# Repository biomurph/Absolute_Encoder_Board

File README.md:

#DEVELOPMENT BRANCH

# Absolute Encoder Board
Welcome to the Open-Source Absolute Encoder Board Repository. Here you will find hardware designs and files that support the Absolute Encoder. The [GrayCode Arduino Library](https://github.com/biomurph/GrayCode) is available for installation via the Arduino IDE, just do a search for GrayCode in the Libraries Manager 

## What is it?
Encoders come in different types. Most people are familiar with [quadrature encoders](https://en.wikipedia.org/wiki/Incremental_encoder#Quadrature_outputs), which use two pins that change state sequentially in different order depending on the direction of rotation. One of the limitations of quadrature is that a microcontroller needs to be paying attention (usually with pin-change interrupts) in order to keep track of each step and count accordingly CW or CCW steps. In certain applications, the need for interrupts and constant attention to the encoder pin change can be limiting. Enter the Absolute encoder. This device can have 3 or more pins that maintain their coded state to show their rotational position. That means that any time you want to, you can read the encoder pins and get the correct positon without having to always keep track. Wikipedia has a great [Gray Code Page](https://en.wikipedia.org/wiki/Gray_code) for those who want to deep dive.

Why would you want an absolute encoder over a quadrature encoder?

- You are using a Raspberry Pi or other single board computer. These are powerful devices, but they run their software under an operating system which can make it hard to catch fast changes in a quadrature signal. All you need is one missed step to be off track. 
- You have encoder inputs but no room or overhead to provide the user dynamic feedback. Say you have a couple of dials on your project box, with a sticker or other static indicator of dial position. The absolute encoder will reliably report it's rotational position whenever asked, without having to keep track of dial movement.

Those two reasons are good enough for me! 

## How does it work?
The encoders in this project use [Gray](https://en.wikipedia.org/wiki/Gray_code) code, also know has Reflected Binary code. It was invented in order to avoid electro-mechanical glitches in rotary circuits. A rotary switch, for example that has 4 pins which output a binary coded decimal (BCD) may have more than one pin (bit) changing state during a transition between positions. This means that it can be possible to misread the rotational position at the transition point between rotational sections. With Gray code, only one bit is changed during each rotational transition, making it far more stable and resistant to glitches and bad readings. Here is a chart of Decimal, Binary, and Grey encoding.

Decimal  | Binary  | Gray
-------- | ------- | -----
0  | 0000 | 0000
1  | 0001 | 0001
2  | 0010 | 0011
3  | 0011 | 0010
4  | 0100 | 0110
5  | 0101 | 0111
6  | 0110 | 0101
7  | 0111 | 0100
8  | 1000 | 1100
9  | 1001 | 1101
10  | 1010 | 1111
11  | 1011 | 1110
12  | 1100 | 1010
13  | 1101 | 1011
14  | 1110 | 1001
15  | 1111 | 1000

Here's another rendering of the Gray code, arranged in a circle. This is the bit pattern of the dial, counting up when it is traveled clockwise.

## Hardware

The hardware is in prototype stage. I am using the [PAC18R](https://github.com/biomurph/Absolute_Encoder_Board/blob/main/assets/pac18r-2511013.pdf) Absolute Encoder from Bourns. They have a 5 pin output, 4 signal pins and 1 common pin, and come in 8 or 16 switch positions. These encoders have detents, which means they 'snap' into rotational position much like an old CRT television set knob does. The board design will carry 2 encoders and use a PISO shift register to read their positions. SW1 position data is in the low nibble, and SW2 data is in the high nibble. These boards can be daisy-chained, and the GrayCode library is designed to read off as many encoder boards as you have connected. The distance between the encoders is 35mm (1 3/8") on center.

### ENCODER SWITCH ORIANTATION

The PAC18R comes in 8, 12, and 16 position variants. I have not seen the 12 position switch widely available, but the GrayCode library will handle it if you come across one. The shafts on them are 6mm diameter and flatted D type. The flatted side, if you are relying on it, is positioned differently relative to the 0 (zero) position. Here's a diagram showing where the flatted position of the shaft is at position 0 for each switch relative to the PCB. 

**NOTE: The 12 position variant has the same flatted D orientation as the 16 position variant**

### PIN CONNECTIONS

There are 6 pins on each end of the board which allow for daisy-chaining mulitiple boards together. The Inhibit pin is pulled LOW  on the board, so you don't need to use it unless you need to use it (HIGH is Inhibit, LOW is Hibit). 
The pinout on the left edge is as follows:

Pin Name  |  Function
:--------:  |  :--------:
+V  |  Positive Voltage Input: 3V to 6V
GND  |  Connect to Voltage Ground
CLK  |  Shift Register Clock Pin
L  |  Shift Register Load Pin
SER_OUT  |  Shift Register Serial Out Pin
INH  |  Shift Register Inhibit Pin

The only difference with the pinout on the right edge is the SER_IN pin. When daisy-chaining, connect the +V, GND, CLK, L pins, and the SER IN of the first board to the SER OUT of the next board, and so on.

Here is the schematic

Here is a photo of the production ready prototype

Absolute Encocder Documentation © 2024 by Joel Murphy is licensed under [CC BY 4.0](https://creativecommons.org/licenses/by/4.0/?ref=chooser-v1)

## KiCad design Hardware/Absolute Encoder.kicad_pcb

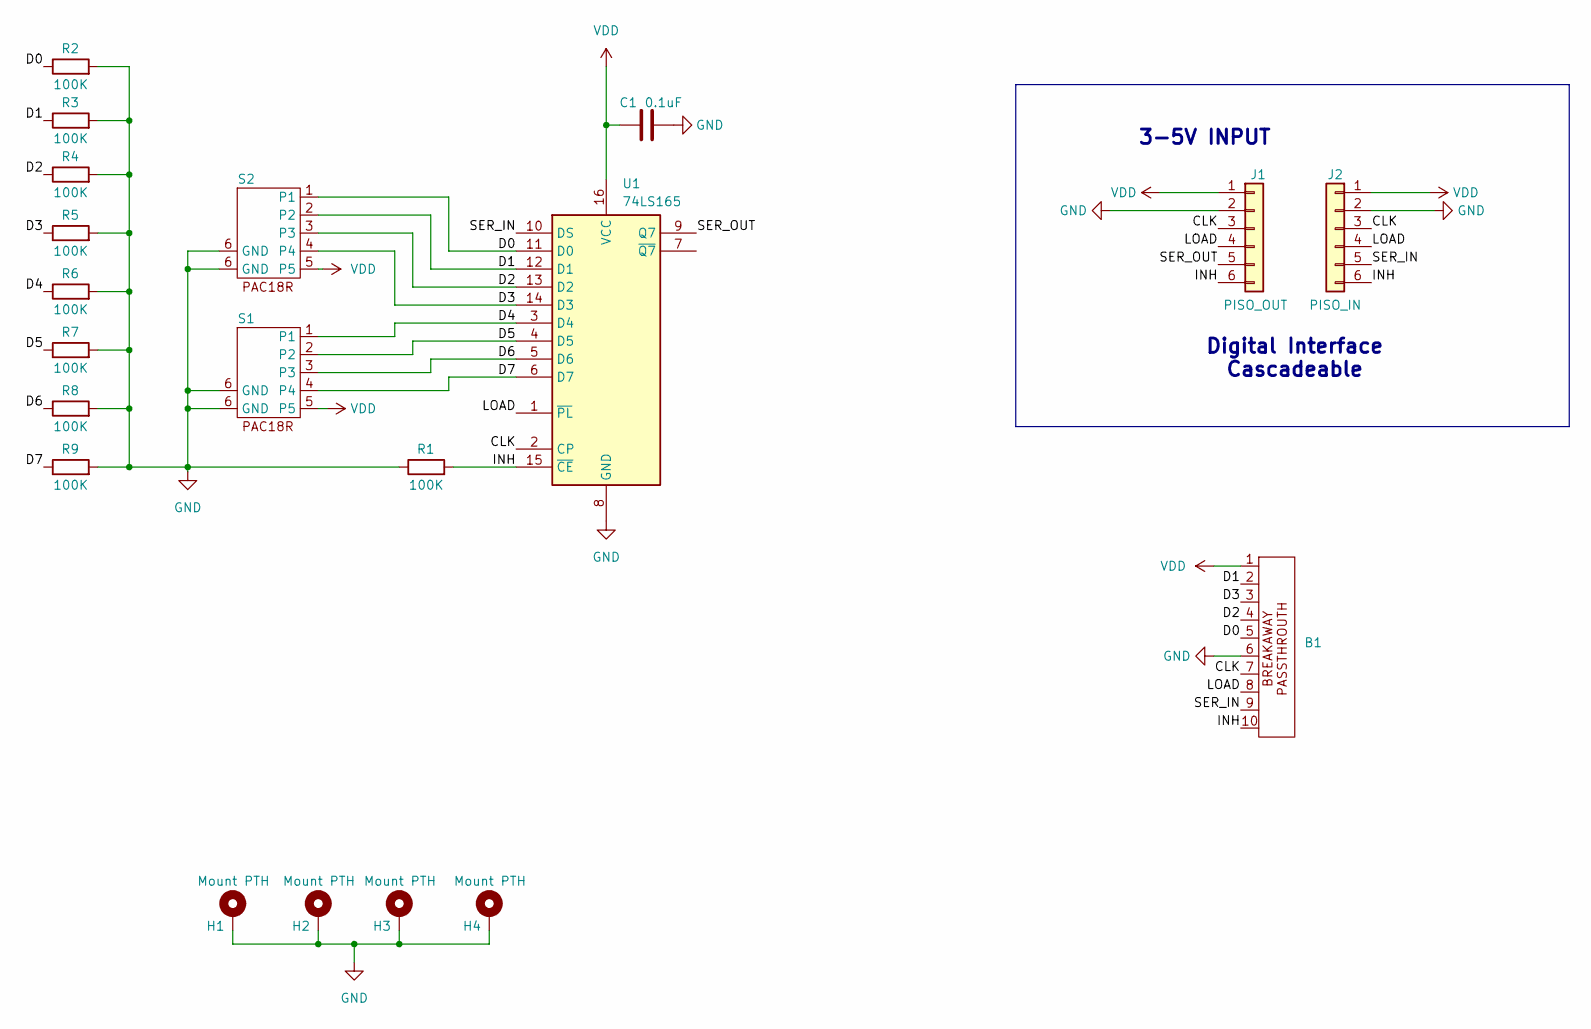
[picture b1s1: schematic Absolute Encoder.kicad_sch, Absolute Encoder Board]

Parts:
B1: Breakaway_10pos
C1: 0.1uF; C_0603_1608Metric
H1, H2, H3, H4: Mount PTH; MountingHole_2.2mm_M2_Pad_TopBottom
J1: PISO_OUT; PinHeader_1x06_P2.54mm_Vertical
J2: PISO_IN; PinHeader_1x06_P2.54mm_Vertical
R1, R2, R3, R4, R5, R6, R7, R8, R9: 100K; R_0603_1608Metric
S1, S2: PAC18R
U1: 74LS165; SOIC-16_3.9x9.9mm_P1.27mm

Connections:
/CLK: B1.7, J1.3, J2.3, U1.2 (CP)
/D0: B1.5, R2.1, S2.1, U1.11 (D0)
/D1: B1.2, R3.1, S2.2, U1.12 (D1)
/D2: B1.4, R4.1, S2.3, U1.13 (D2)
/D3: B1.3, R5.1, S2.4, U1.14 (D3)
/D4: R6.1, S1.1, U1.3 (D4)
/D5: R7.1, S1.2, U1.4 (D5)
/D6: R8.1, S1.3, U1.5 (D6)
/D7: R9.1, S1.4, U1.6 (D7)
/INH: B1.10, J1.6, J2.6, R1.2, U1.15 (~CE)
/LOAD: B1.8, J1.4, J2.4, U1.1 (~PL)
/SER_IN: B1.9, J2.5, U1.10 (DS)
/SER_OUT: J1.5, U1.9 (Q7)
GND: B1.6, C1.2, H1.1, H2.1, H3.1, H4.1, J1.2, J2.2, R1.1, R2.2, R3.2, R4.2, R5.2, R6.2, R7.2, R8.2, R9.2, S1.6 (GND), S2.6 (GND), U1.8 (GND)
VDD: B1.1, C1.1, J1.1, J2.1, S1.5, S2.5, U1.16 (VCC)

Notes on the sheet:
Digital Interface Cascadeable
3-5V INPUT

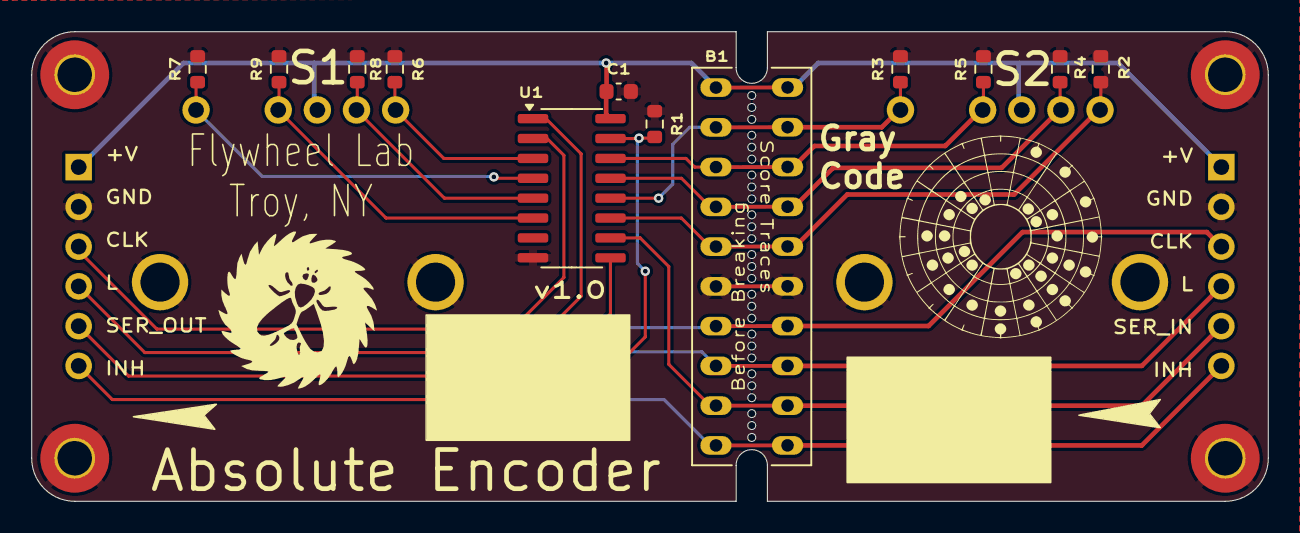
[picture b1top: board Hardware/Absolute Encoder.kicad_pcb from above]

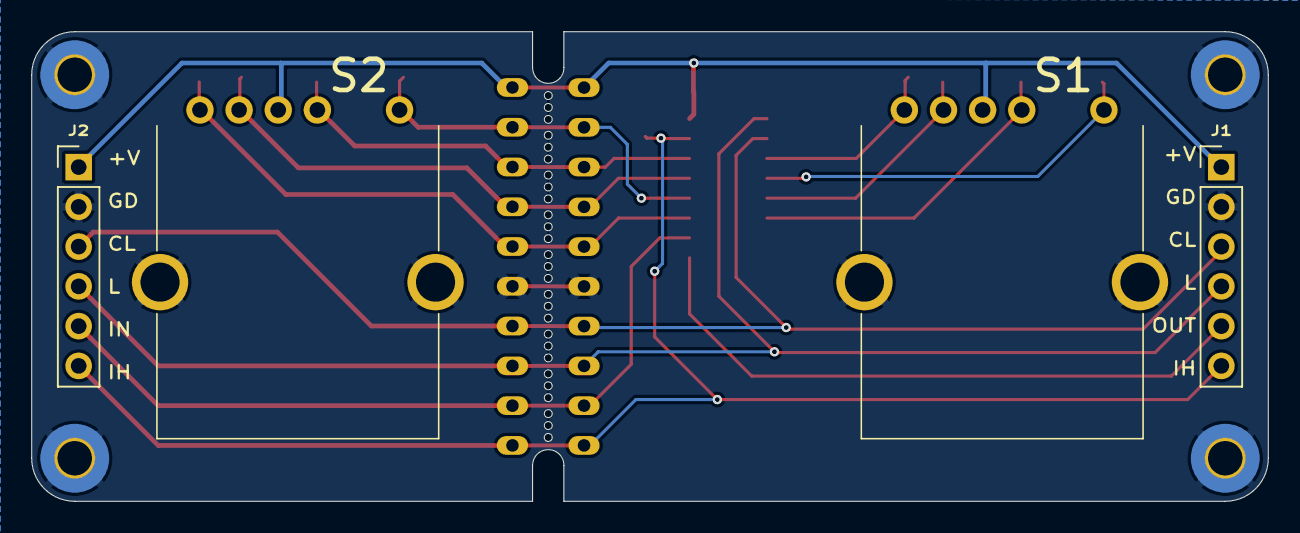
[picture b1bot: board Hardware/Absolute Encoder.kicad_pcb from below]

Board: 2 copper layers, 79.0 x 30.0 mm, 20 parts (4 on the bottom side), 15 nets.

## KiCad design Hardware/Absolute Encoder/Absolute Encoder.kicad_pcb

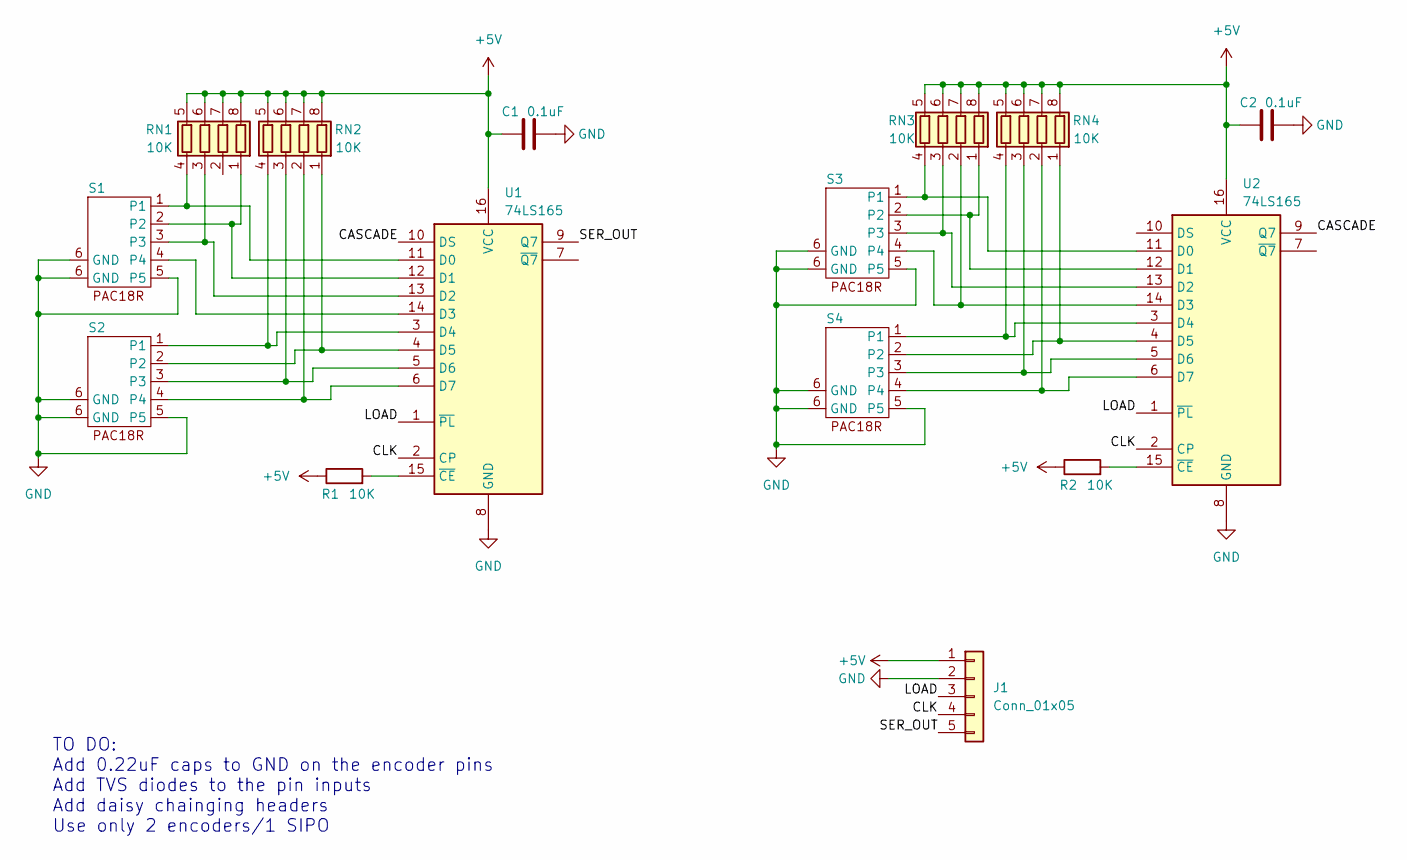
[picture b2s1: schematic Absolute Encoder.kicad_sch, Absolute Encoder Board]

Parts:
C1, C2: 0.1uF; C_0603_1608Metric
J1: Conn_01x05; PinHeader_1x05_P2.54mm_Vertical
R1, R2: 10K; R_0603_1608Metric
RN1, RN2, RN3, RN4: 10K; R_Array_Concave_4x0402
S1, S2, S3, S4: PAC18R
U1, U2: 74LS165; SOIC-16_3.9x9.9mm_P1.27mm

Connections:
+5V: C1.1, C2.1, J1.1, R1.1, R2.1, RN1.5 (R4.2), RN1.6 (R3.2), RN1.7 (R2.2), RN1.8 (R1.2), RN2.5 (R4.2), RN2.6 (R3.2), RN2.7 (R2.2), RN2.8 (R1.2), RN3.5 (R4.2), RN3.6 (R3.2), RN3.7 (R2.2), RN3.8 (R1.2), RN4.5 (R4.2), RN4.6 (R3.2), RN4.7 (R2.2), RN4.8 (R1.2), U1.16 (VCC), U2.16 (VCC)
/CASCADE: U1.10 (DS), U2.9 (Q7)
/CLK: J1.4, U1.2 (CP), U2.2 (CP)
/LOAD: J1.3, U1.1 (~PL), U2.1 (~PL)
/SER_OUT: J1.5, U1.9 (Q7)
GND: C1.2, C2.2, J1.2, S1.5, S1.6 (GND), S2.5, S2.6 (GND), S3.5, S3.6 (GND), S4.5, S4.6 (GND), U1.8 (GND), U2.8 (GND)
unnamed: RN1.1 (R1.1), S1.2, U1.12 (D1)
unnamed: RN1.3 (R3.1), S1.3, U1.13 (D2)
unnamed: RN1.4 (R4.1), S1.1, U1.11 (D0)
unnamed: RN2.1 (R1.1), S2.2, U1.4 (D5)
unnamed: RN2.2 (R2.1), S2.4, U1.6 (D7)
unnamed: RN2.3 (R3.1), S2.3, U1.5 (D6)
unnamed: RN2.4 (R4.1), S2.1, U1.3 (D4)
unnamed: RN3.1 (R1.1), S3.2, U2.12 (D1)
unnamed: RN3.2 (R2.1), S3.4, U2.14 (D3)
unnamed: RN3.3 (R3.1), S3.3, U2.13 (D2)
unnamed: RN3.4 (R4.1), S3.1, U2.11 (D0)
unnamed: RN4.1 (R1.1), S4.2, U2.4 (D5)
unnamed: RN4.2 (R2.1), S4.4, U2.6 (D7)
unnamed: RN4.3 (R3.1), S4.3, U2.5 (D6)
unnamed: RN4.4 (R4.1), S4.1, U2.3 (D4)
unnamed: R1.2, U1.15 (~CE)
unnamed: R2.2, U2.15 (~CE)

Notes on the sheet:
TO DO: Add 0.22uF caps to GND on the encoder pins Add TVS diodes to the pin inputs Add daisy chainging headers Use only 2 encoders/1 SIPO

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
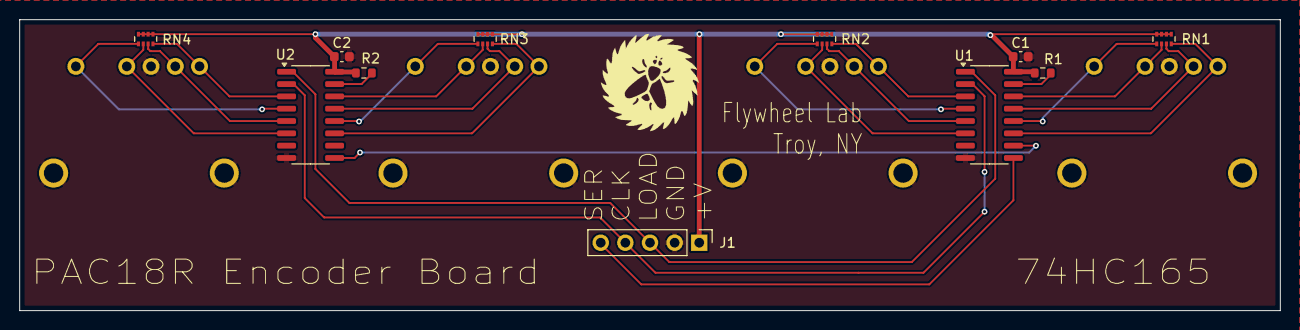
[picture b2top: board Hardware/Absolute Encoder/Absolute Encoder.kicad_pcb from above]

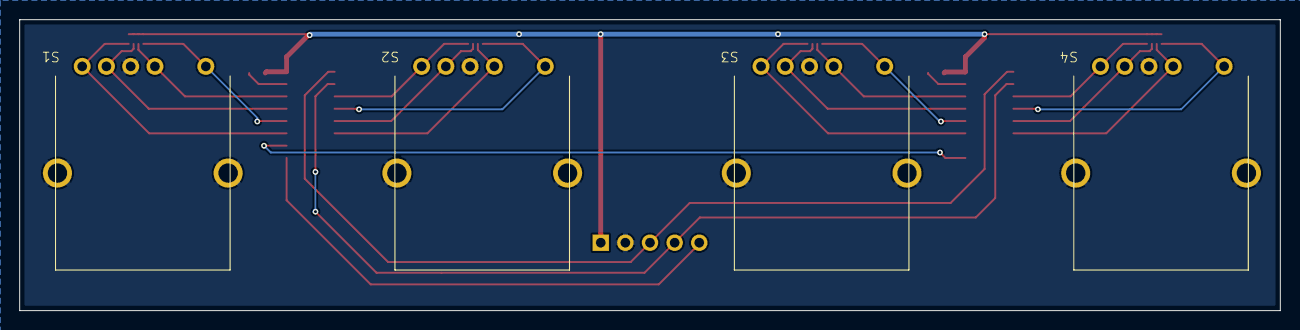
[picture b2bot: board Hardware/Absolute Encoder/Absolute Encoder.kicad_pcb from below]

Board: 2 copper layers, 130.0 x 30.0 mm, 15 parts (4 on the bottom side), 24 nets.

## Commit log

2024-09-16 Added mount holes
    First draft of the silk
    Mount Holes
2024-09-16 Tidied up files, added assets
2024-09-17 change R network for individual Rs
2024-09-17 Improving layout, readme update
2024-09-18 readme update
2024-09-18 fixing schematic render
2024-11-11 added photos and updated readme
2024-12-03 Update Readme
    add license
2024-12-10 updated back silk
2024-12-10 Moved custom parts to local path
2024-12-10 removed erroneous text
2024-12-10 Added breakaway and set encoder distance
